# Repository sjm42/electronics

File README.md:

# Electronics
My various electronics projects

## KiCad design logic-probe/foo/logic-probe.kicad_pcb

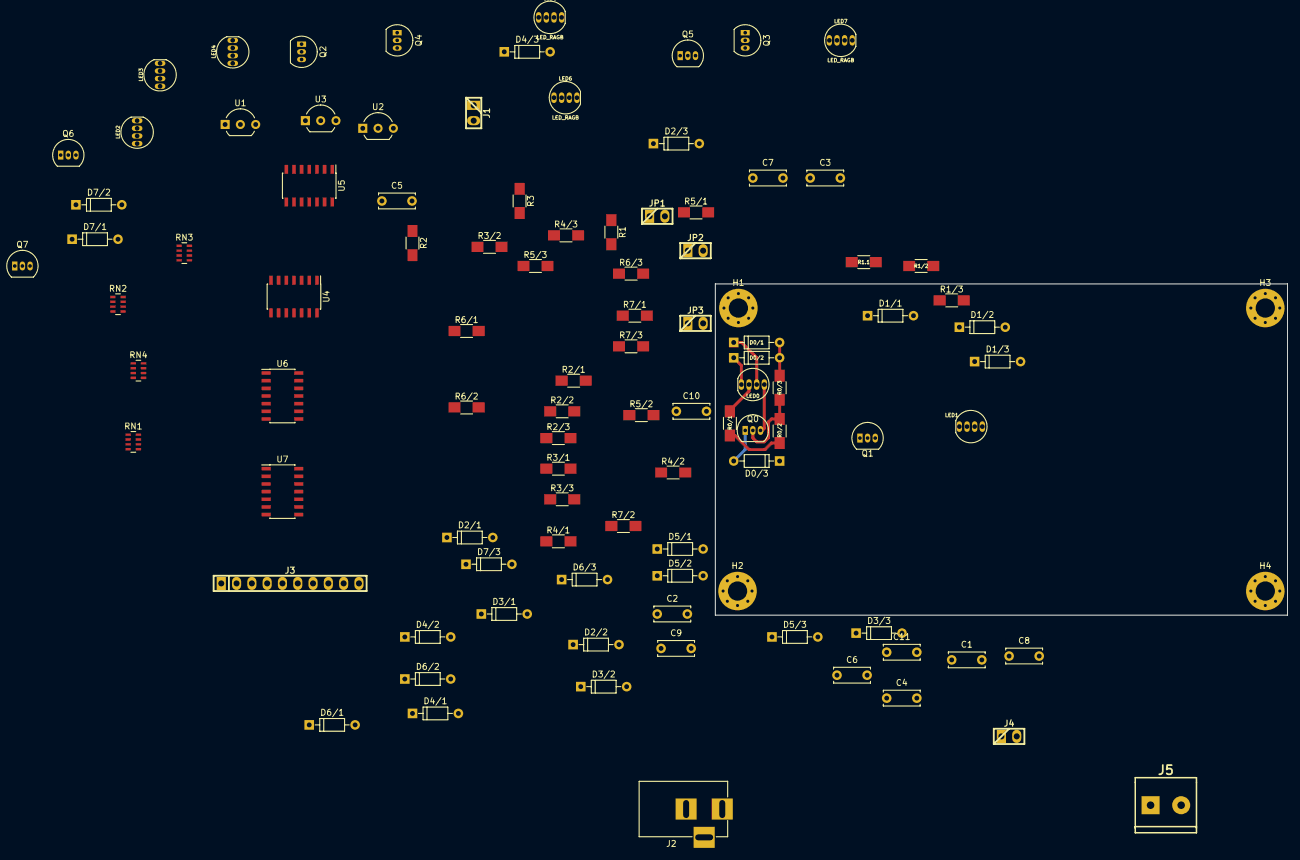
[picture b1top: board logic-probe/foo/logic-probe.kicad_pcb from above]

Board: 2 copper layers, 95.0 x 55.0 mm, 101 parts (0 on the bottom side), 72 nets.

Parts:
C1: 10u; C_Disc_D6.0mm_W2.5mm_P5.00mm
C2, C4, C6: 4.7u; C_Disc_D6.0mm_W2.5mm_P5.00mm
C3, C5, C7, C8, C9, C10, C11: 1u; C_Disc_D6.0mm_W2.5mm_P5.00mm
D0/1, D0/2, D0/3, D1/1, D1/2, D1/3, D2/1, D2/2, D2/3, D3/1, D3/2, D3/3, D4/1, D4/2, D4/3, D5/1, D5/2, D5/3, D6/1, D6/2, D6/3, D7/1, D7/2, D7/3: 1N4148; D_DO-35_SOD27_P7.62mm_Horizontal
H1, H2, H3, H4: MountingHole; MountingHole_3.2mm_M3_Pad_Via
J1, J4: Conn_01x02_Male; pin_strip_2
J2: dc_jack; BARREL_JACK
J3: Conn_01x10_Male; pin_strip_10
J5: Screw_Terminal_01x02; mors_2p
JP1, JP2, JP3: Jumper; pin_strip_2
LED0, LED1, LED2, LED3, LED4, LED5, LED6, LED7: LED_RAGB; LED-RGB-THRU
Q0, Q1, Q2, Q3, Q4, Q5, Q6, Q7: 2N2222A; TO-92_Inline_Narrow_Oval
R0/1, R1.1, R2/1, R3/1, R4/1, R5/1, R6/1, R7/1: 470; R_1206_HandSoldering
R0/2, R1/2, R2/2, R3/2, R4/2, R5/2, R6/2, R7/2: 47k; R_1206_HandSoldering
R0/3, R1/3, R2/3, R3/3, R4/3, R5/3, R6/3, R7/3: 100; R_1206_HandSoldering
R1, R3: 7.5k; R_1206_HandSoldering
R2: 10k; R_1206_HandSoldering
RN1, RN2, RN3, RN4: 220k; R_Array_Concave_4x0603
U1: L78L05_TO92; TO-92_Inline_Wide
U2: L78L10_TO92; TO-92_Inline_Wide
U3: L78L15_TO92; TO-92_Inline_Wide
U4, U5, U6, U7: LM339; SOIC-14_3.9x8.7mm_Pitch1.27mm

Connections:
/V_5V: C3.1, JP1.1, U1.1
/V_10V: C5.1, JP2.1, U2.1
/V_15V: C7.1, JP3.1, U3.1
/V_IN: C1.1, C2.1, C4.1, C6.1, J1.1, J2.3, U1.3, U2.3, U3.3
/bits/0_HI: D0/1.1, LED0.3, U4.1
/bits/0_LO: D0/2.1, LED0.1, U4.2
/bits/1_HI: D1/1.1, LED1.3, U4.13
/bits/1_LO: D1/2.1, LED1.1, U4.14
/bits/2_HI: D2/1.1, LED2.3, U5.1
/bits/2_LO: D2/2.1, LED2.1, U5.2
/bits/3_HI: D3/1.1, LED3.3, U5.13
/bits/3_LO: D3/2.1, LED3.1, U5.14
/bits/4_HI: D4/1.1, LED4.3, U6.1
/bits/4_LO: D4/2.1, LED4.1, U6.2
/bits/5_HI: D5/1.1, LED5.3, U6.13
/bits/5_LO: D5/2.1, LED5.1, U6.14
/bits/6_HI: D6/1.1, LED6.3, U7.1
/bits/6_LO: D6/2.1, LED6.1, U7.2
/bits/7_HI: D7/1.1, LED7.3, U7.13
/bits/7_LO: D7/2.1, LED7.1, U7.14
GND: C1.2, C2.2, C3.2, C4.2, C5.2, C6.2, C7.2, C8.2, C9.2, C10.2, C11.2, D0/3.1, D1/3.1, D2/3.1, D3/3.1, D4/3.1, D5/3.1, D6/3.1, D7/3.1, J1.2, J2.1, J2.2, J3.10, J4.2, J5.2, R3.2, RN2.1, RN2.2, RN2.3, RN2.4, RN4.1, RN4.2, RN4.3, RN4.4, U1.2, U2.2, U3.2, U4.12, U5.12, U6.12, U7.12
IN_0: J3.1, RN1.1, RN2.8, U4.5, U4.6
IN_1: J3.2, RN1.2, RN2.7, U4.9, U4.10
IN_2: J3.3, RN1.3, RN2.6, U5.5, U5.6
IN_3: J3.4, RN1.4, RN2.5, U5.9, U5.10
IN_4: J3.5, RN3.1, RN4.8, U6.5, U6.6
IN_5: J3.6, RN3.2, RN4.7, U6.9, U6.10
IN_6: J3.7, RN3.3, RN4.6, U7.5, U7.6
IN_7: J3.8, RN3.4, RN4.5, U7.9, U7.10
unnamed: D0/1.2, D0/2.2, R0/3.1
unnamed: D0/3.2, Q0.1
unnamed: D1/1.2, D1/2.2, R1/3.1
unnamed: D1/3.2, Q1.1
unnamed: D2/1.2, D2/2.2, R2/3.1
unnamed: D2/3.2, Q2.1
unnamed: D3/1.2, D3/2.2, R3/3.1
unnamed: D3/3.2, Q3.1
unnamed: D4/1.2, D4/2.2, R4/3.1
unnamed: D4/3.2, Q4.1
unnamed: D5/1.2, D5/2.2, R5/3.1
unnamed: D5/3.2, Q5.1
unnamed: D6/1.2, D6/2.2, R6/3.1
unnamed: D6/3.2, Q6.1
unnamed: D7/1.2, D7/2.2, R7/3.1
unnamed: D7/3.2, Q7.1
unnamed: LED0.2, R0/1.1
unnamed: LED0.4, Q0.3
unnamed: LED1.2, R1.1.1
unnamed: LED1.4, Q1.3
unnamed: LED2.2, R2/1.1
unnamed: LED2.4, Q2.3
unnamed: LED3.2, R3/1.1
unnamed: LED3.4, Q3.3
unnamed: LED4.2, R4/1.1
unnamed: LED4.4, Q4.3
unnamed: LED5.2, R5/1.1
unnamed: LED5.4, Q5.3
unnamed: LED6.2, R6/1.1
unnamed: LED6.4, Q6.3
unnamed: LED7.2, R7/1.1
unnamed: LED7.4, Q7.3
unnamed: Q0.2, R0/2.1, R0/3.2
unnamed: Q1.2, R1/2.1, R1/3.2
unnamed: Q2.2, R2/2.1, R2/3.2
unnamed: Q3.2, R3/2.1, R3/3.2
unnamed: Q4.2, R4/2.1, R4/3.2
unnamed: Q5.2, R5/2.1, R5/3.2
unnamed: Q6.2, R6/2.1, R6/3.2
unnamed: Q7.2, R7/2.1, R7/3.2
VCC: C8.1, C9.1, C10.1, C11.1, J3.9, J4.1, J5.1, JP1.2, JP2.2, JP3.2, R0/1.2, R0/2.2, R1.1, R1.1.2, R1/2.2, R2/1.2, R2/2.2, R3/1.2, R3/2.2, R4/1.2, R4/2.2, R5/1.2, R5/2.2, R6/1.2, R6/2.2, R7/1.2, R7/2.2, RN1.5, RN1.6, RN1.7, RN1.8, RN3.5, RN3.6, RN3.7, RN3.8, U4.3, U5.3, U6.3, U7.3
V_HI: R1.2, R2.1, U4.7, U4.11, U5.7, U5.11, U6.7, U6.11, U7.7, U7.11
V_LO: R2.2, R3.1, U4.4, U4.8, U5.4, U5.8, U6.4, U6.8, U7.4, U7.8

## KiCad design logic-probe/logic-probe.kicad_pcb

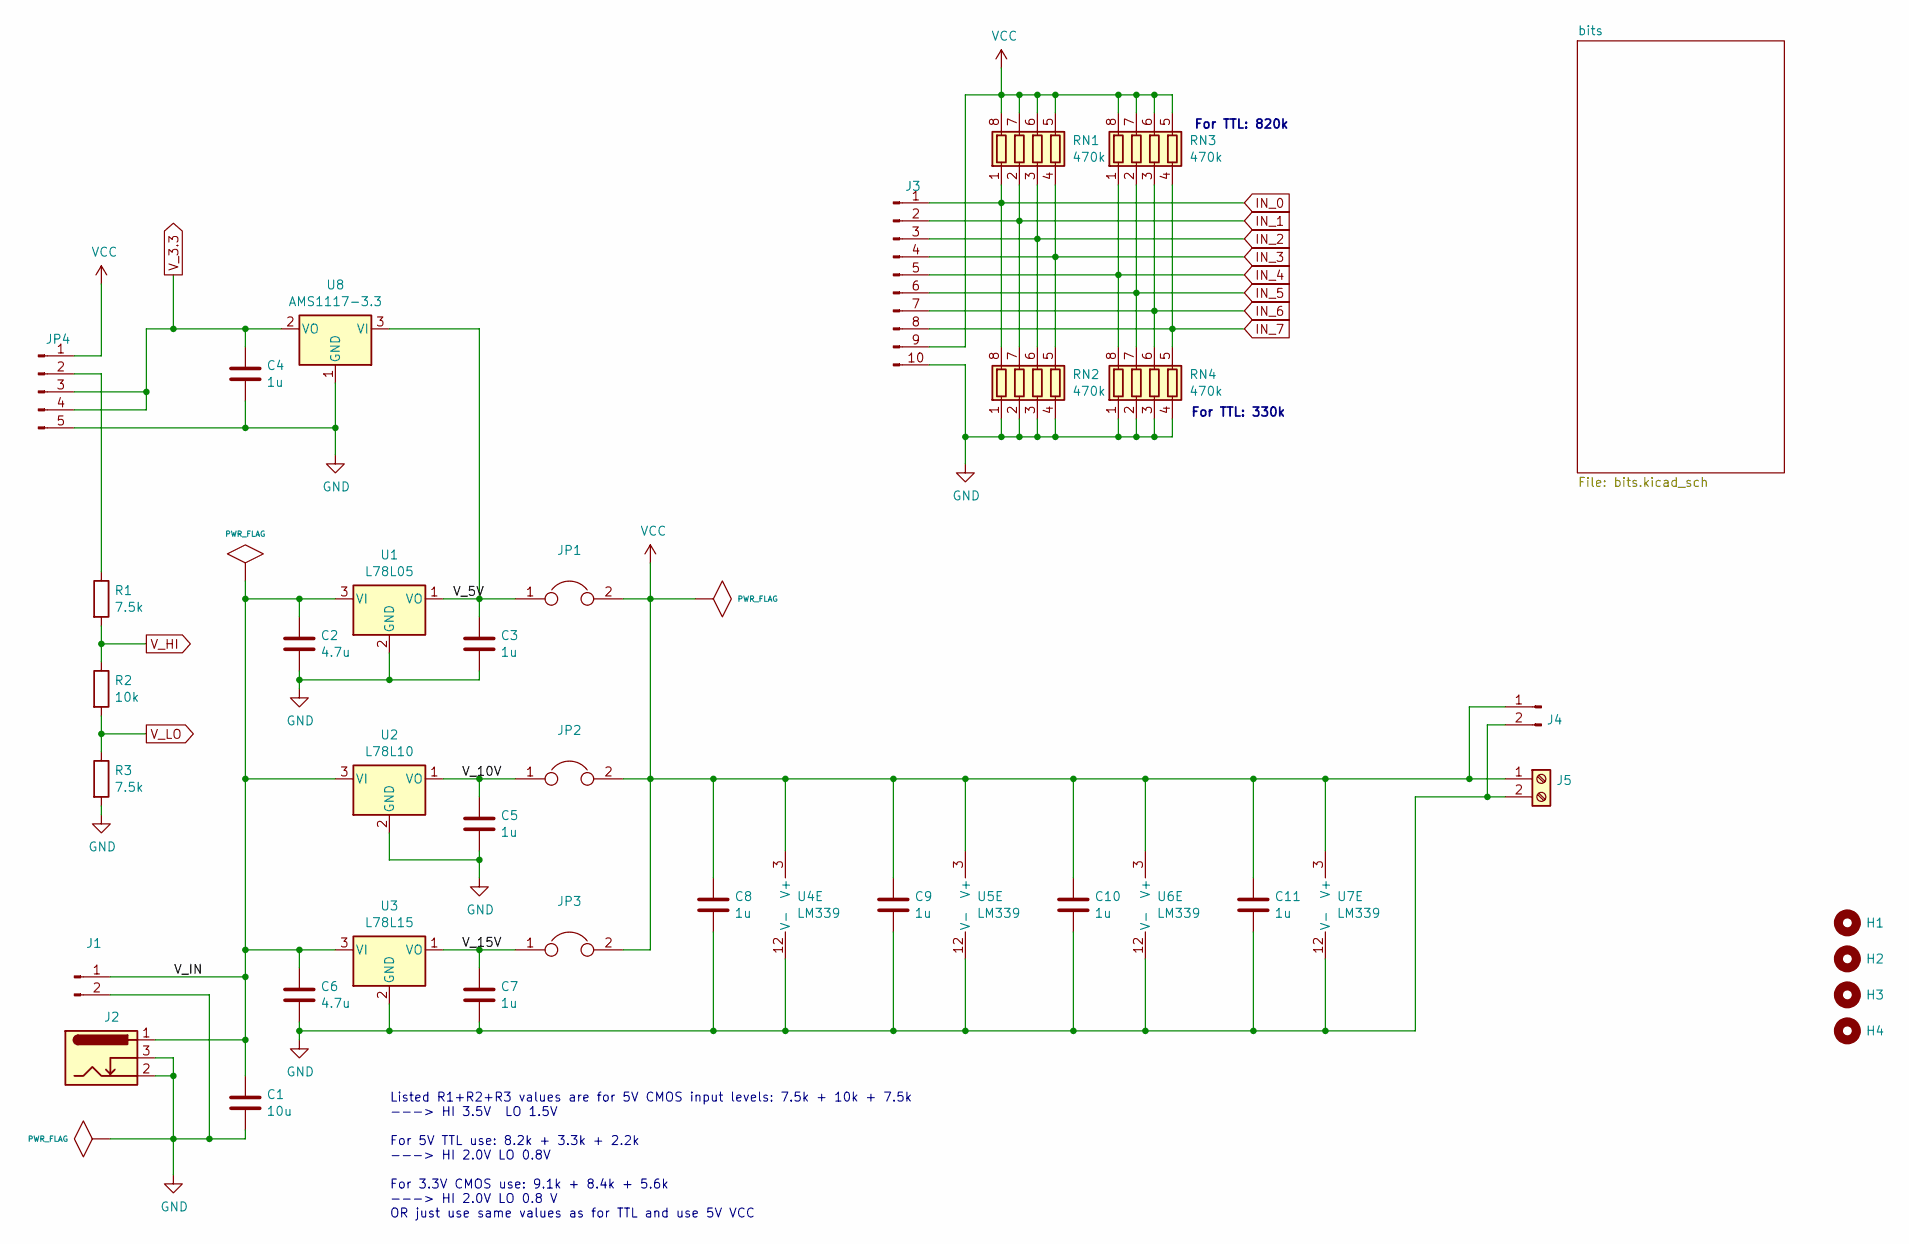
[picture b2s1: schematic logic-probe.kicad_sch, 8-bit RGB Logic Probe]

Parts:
C1: 10u; C_Disc_D6.0mm_W2.5mm_P5.00mm
C2, C6: 4.7u; C_Disc_D6.0mm_W2.5mm_P5.00mm
C3, C4, C5, C7, C8, C9, C10, C11: 1u; C_Disc_D6.0mm_W2.5mm_P5.00mm
H1, H2, H3, H4: MountingHole; MountingHole_3.2mm_M3_Pad_Via
J1, J4: Conn_01x02_Male; pin_strip_2
J2: Barrel_Jack_Switch; BarrelJack_Horizontal
J3: Conn_01x10_Male; pin_strip_10
J5: Screw_Terminal_01x02; mors_2p
JP1, JP2, JP3: Jumper; pin_strip_2
JP4: Conn_01x05_Male; pin_strip_5
R1, R3: 7.5k; R_1206_HandSoldering
R2: 10k; R_1206_HandSoldering
RN1, RN2, RN3, RN4: 470k; R_Array_Concave_4x0603
U1: L78L05; TO-92_Inline_Wide
U2: L78L10; TO-92_Inline_Wide
U3: L78L15; TO-92_Inline_Wide
U4, U5, U6, U7: LM339; SOIC-14_3.9x8.7mm_Pitch1.27mm
U8: AMS1117-3.3; sot223

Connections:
/V_5V: C3.1, JP1.1, U1.1 (VO), U8.3 (VI)
/V_10V: C5.1, JP2.1, U2.1 (VO)
/V_15V: C7.1, JP3.1, U3.1 (VO)
/V_IN: C1.1, C2.1, C6.1, J1.1, J2.1, U1.3 (VI), U2.3 (VI), U3.3 (VI)
GND: C1.2, C2.2, C3.2, C4.2, C5.2, C6.2, C7.2, C8.2, C9.2, C10.2, C11.2, J1.2, J2.2, J2.3, J3.10, J4.2, J5.2, JP4.5, R3.2, RN2.1 (R1.1), RN2.2 (R2.1), RN2.3 (R3.1), RN2.4 (R4.1), RN4.1 (R1.1), RN4.2 (R2.1), RN4.3 (R3.1), RN4.4 (R4.1), U1.2 (GND), U2.2 (GND), U3.2 (GND), U4.12 (V-), U5.12 (V-), U6.12 (V-), U7.12 (V-), U8.1 (GND); also elsewhere on the board
IN_0: J3.1, RN1.1 (R1.1), RN2.8 (R1.2); also elsewhere on the board
IN_1: J3.2, RN1.2 (R2.1), RN2.7 (R2.2); also elsewhere on the board
IN_2: J3.3, RN1.3 (R3.1), RN2.6 (R3.2); also elsewhere on the board
IN_3: J3.4, RN1.4 (R4.1), RN2.5 (R4.2); also elsewhere on the board
IN_4: J3.5, RN3.1 (R1.1), RN4.8 (R1.2); also elsewhere on the board
IN_5: J3.6, RN3.2 (R2.1), RN4.7 (R2.2); also elsewhere on the board
IN_6: J3.7, RN3.3 (R3.1), RN4.6 (R3.2); also elsewhere on the board
IN_7: J3.8, RN3.4 (R4.1), RN4.5 (R4.2); also elsewhere on the board
unnamed: JP4.2, R1.1
VCC: C8.1, C9.1, C10.1, C11.1, J3.9, J4.1, J5.1, JP1.2, JP2.2, JP3.2, JP4.1, RN1.5 (R4.2), RN1.6 (R3.2), RN1.7 (R2.2), RN1.8 (R1.2), RN3.5 (R4.2), RN3.6 (R3.2), RN3.7 (R2.2), RN3.8 (R1.2), U4.3 (V+), U5.3 (V+), U6.3 (V+), U7.3 (V+); also elsewhere on the board
V_3.3: C4.1, JP4.3, JP4.4, U8.2 (VO)
V_HI: R1.2, R2.1; also elsewhere on the board
V_LO: R2.2, R3.1; also elsewhere on the board

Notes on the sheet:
For TTL: 820k
Listed R1+R2+R3 values are for 5V CMOS input levels: 7.5k + 10k + 7.5k ---> HI 3.5V LO 1.5V For 5V TTL use: 8.2k + 3.3k + 2.2k ---> HI 2.0V LO 0.8V For 3.3V CMOS use: 9.1k + 8.4k + 5.6k ---> HI 2.0V LO 0.8 V OR just use same values as for TTL and use 5V VCC
For TTL: 330k

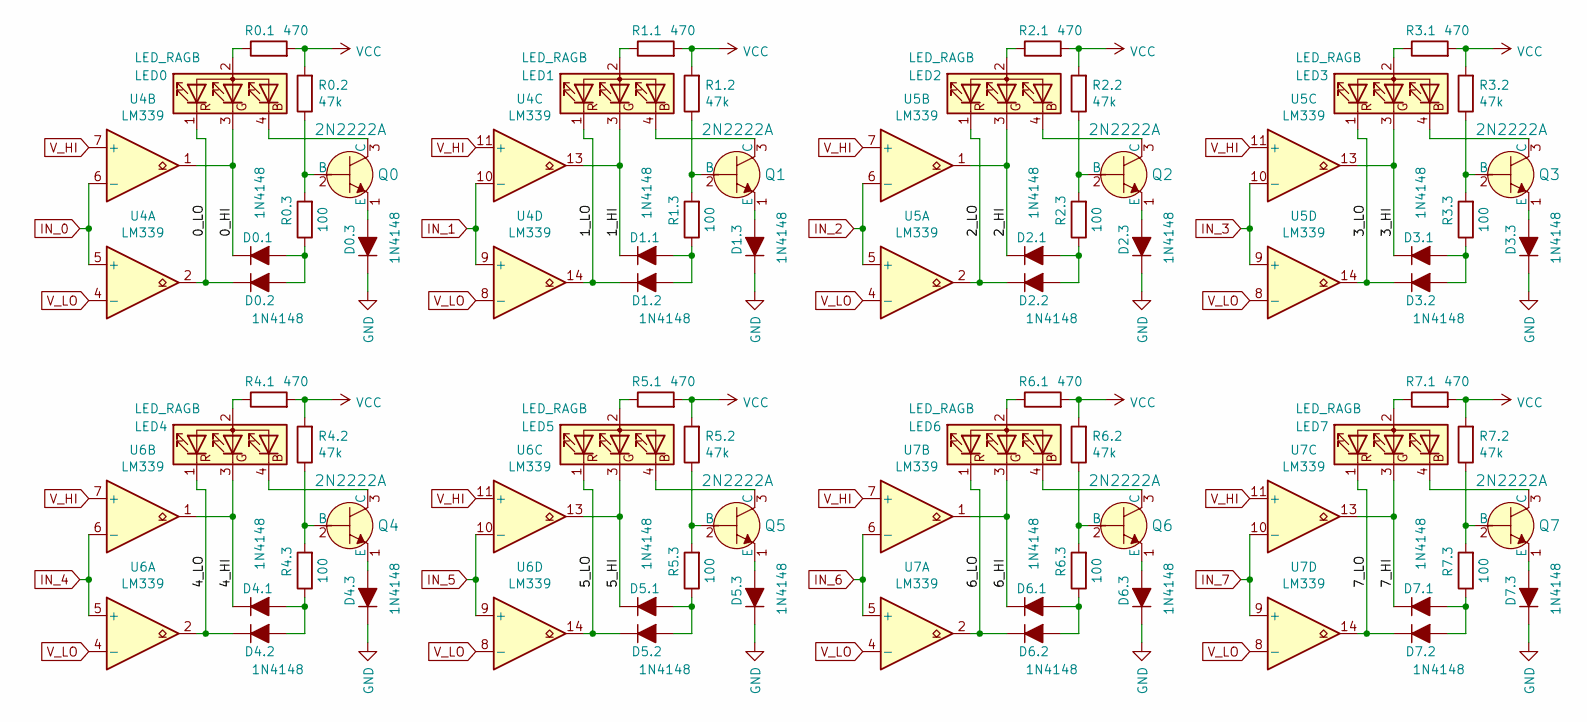
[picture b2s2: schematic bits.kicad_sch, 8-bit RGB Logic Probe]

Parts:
D0.1, D0.2, D0.3, D1.1, D1.2, D1.3, D2.1, D2.2, D2.3, D3.1, D3.2, D3.3, D4.1, D4.2, D4.3, D5.1, D5.2, D5.3, D6.1, D6.2, D6.3, D7.1, D7.2, D7.3: 1N4148; D_T-1_P5.08mm_Horizontal
LED0, LED1, LED2, LED3, LED4, LED5, LED6, LED7: LED_RAGB; LED-RGB-THRU
Q0, Q1, Q2, Q3, Q4, Q5, Q6, Q7: 2N2222A; TO-92_Inline_Narrow_Oval; MPN 2N2222A; Digi-Key_PN 2N2222ACS-ND
R0.1, R1.1, R2.1, R3.1, R4.1, R5.1, R6.1, R7.1: 470; R_1206_HandSoldering
R0.2, R1.2, R2.2, R3.2, R4.2, R5.2, R6.2, R7.2: 47k; R_1206_HandSoldering
R0.3, R1.3, R2.3, R3.3, R4.3, R5.3, R6.3, R7.3: 100; R_1206_HandSoldering
U4, U5, U6, U7: LM339; SOIC-14_3.9x8.7mm_Pitch1.27mm

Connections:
/bits/0_HI: D0.1.1 (K), LED0.3 (GK), U4.1
/bits/0_LO: D0.2.1 (K), LED0.1 (RK), U4.2
/bits/1_HI: D1.1.1 (K), LED1.3 (GK), U4.13
/bits/1_LO: D1.2.1 (K), LED1.1 (RK), U4.14
/bits/2_HI: D2.1.1 (K), LED2.3 (GK), U5.1
/bits/2_LO: D2.2.1 (K), LED2.1 (RK), U5.2
/bits/3_HI: D3.1.1 (K), LED3.3 (GK), U5.13
/bits/3_LO: D3.2.1 (K), LED3.1 (RK), U5.14
/bits/4_HI: D4.1.1 (K), LED4.3 (GK), U6.1
/bits/4_LO: D4.2.1 (K), LED4.1 (RK), U6.2
/bits/5_HI: D5.1.1 (K), LED5.3 (GK), U6.13
/bits/5_LO: D5.2.1 (K), LED5.1 (RK), U6.14
/bits/6_HI: D6.1.1 (K), LED6.3 (GK), U7.1
/bits/6_LO: D6.2.1 (K), LED6.1 (RK), U7.2
/bits/7_HI: D7.1.1 (K), LED7.3 (GK), U7.13
/bits/7_LO: D7.2.1 (K), LED7.1 (RK), U7.14
GND: D0.3.1 (K), D1.3.1 (K), D2.3.1 (K), D3.3.1 (K), D4.3.1 (K), D5.3.1 (K), D6.3.1 (K), D7.3.1 (K); also elsewhere on the board
IN_0: U4.5 (+), U4.6 (-); also elsewhere on the board
IN_1: U4.9 (+), U4.10 (-); also elsewhere on the board
IN_2: U5.5 (+), U5.6 (-); also elsewhere on the board
IN_3: U5.9 (+), U5.10 (-); also elsewhere on the board
IN_4: U6.5 (+), U6.6 (-); also elsewhere on the board
IN_5: U6.9 (+), U6.10 (-); also elsewhere on the board
IN_6: U7.5 (+), U7.6 (-); also elsewhere on the board
IN_7: U7.9 (+), U7.10 (-); also elsewhere on the board
unnamed: D0.1.2 (A), D0.2.2 (A), R0.3.1
unnamed: D0.3.2 (A), Q0.1 (E)
unnamed: D1.1.2 (A), D1.2.2 (A), R1.3.1
unnamed: D1.3.2 (A), Q1.1 (E)
unnamed: D2.1.2 (A), D2.2.2 (A), R2.3.1
unnamed: D2.3.2 (A), Q2.1 (E)
unnamed: D3.1.2 (A), D3.2.2 (A), R3.3.1
unnamed: D3.3.2 (A), Q3.1 (E)
unnamed: D4.1.2 (A), D4.2.2 (A), R4.3.1
unnamed: D4.3.2 (A), Q4.1 (E)
unnamed: D5.1.2 (A), D5.2.2 (A), R5.3.1
unnamed: D5.3.2 (A), Q5.1 (E)
unnamed: D6.1.2 (A), D6.2.2 (A), R6.3.1
unnamed: D6.3.2 (A), Q6.1 (E)
unnamed: D7.1.2 (A), D7.2.2 (A), R7.3.1
unnamed: D7.3.2 (A), Q7.1 (E)
unnamed: LED0.2 (A), R0.1.1
unnamed: LED0.4 (BK), Q0.3 (C)
unnamed: LED1.2 (A), R1.1.1
unnamed: LED1.4 (BK), Q1.3 (C)
unnamed: LED2.2 (A), R2.1.1
unnamed: LED2.4 (BK), Q2.3 (C)
unnamed: LED3.2 (A), R3.1.1
unnamed: LED3.4 (BK), Q3.3 (C)
unnamed: LED4.2 (A), R4.1.1
unnamed: LED4.4 (BK), Q4.3 (C)
unnamed: LED5.2 (A), R5.1.1
unnamed: LED5.4 (BK), Q5.3 (C)
unnamed: LED6.2 (A), R6.1.1
unnamed: LED6.4 (BK), Q6.3 (C)
unnamed: LED7.2 (A), R7.1.1
unnamed: LED7.4 (BK), Q7.3 (C)
unnamed: Q0.2 (B), R0.2.1, R0.3.2
unnamed: Q1.2 (B), R1.2.1, R1.3.2
unnamed: Q2.2 (B), R2.2.1, R2.3.2
unnamed: Q3.2 (B), R3.2.1, R3.3.2
unnamed: Q4.2 (B), R4.2.1, R4.3.2
unnamed: Q5.2 (B), R5.2.1, R5.3.2
unnamed: Q6.2 (B), R6.2.1, R6.3.2
unnamed: Q7.2 (B), R7.2.1, R7.3.2
VCC: R0.1.2, R0.2.2, R1.1.2, R1.2.2, R2.1.2, R2.2.2, R3.1.2, R3.2.2, R4.1.2, R4.2.2, R5.1.2, R5.2.2, R6.1.2, R6.2.2, R7.1.2, R7.2.2; also elsewhere on the board
V_HI: U4.7 (+), U4.11 (+), U5.7 (+), U5.11 (+), U6.7 (+), U6.11 (+), U7.7 (+), U7.11 (+); also elsewhere on the board
V_LO: U4.4 (-), U4.8 (-), U5.4 (-), U5.8 (-), U6.4 (-), U6.8 (-), U7.4 (-), U7.8 (-); also elsewhere on the board

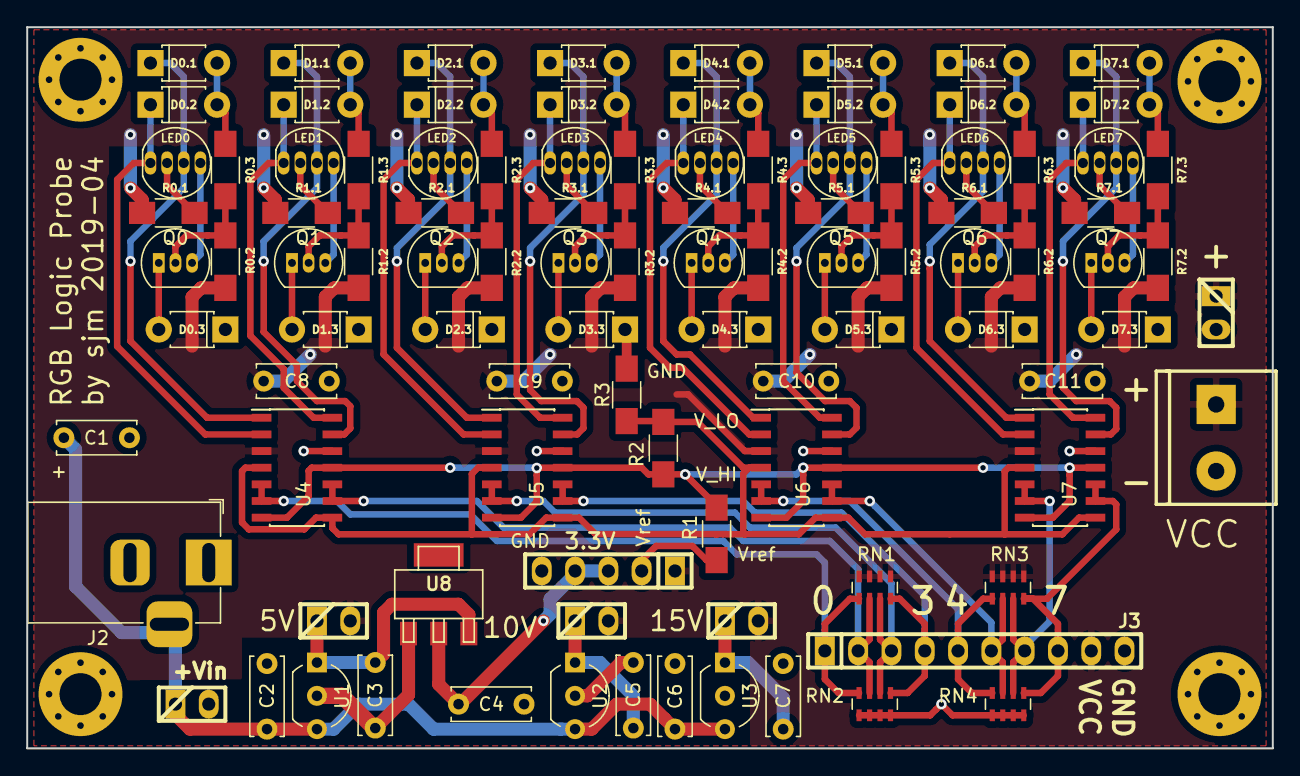
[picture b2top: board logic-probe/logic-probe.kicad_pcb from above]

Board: 2 copper layers, 95.0 x 55.0 mm, 103 parts (0 on the bottom side), 74 nets.

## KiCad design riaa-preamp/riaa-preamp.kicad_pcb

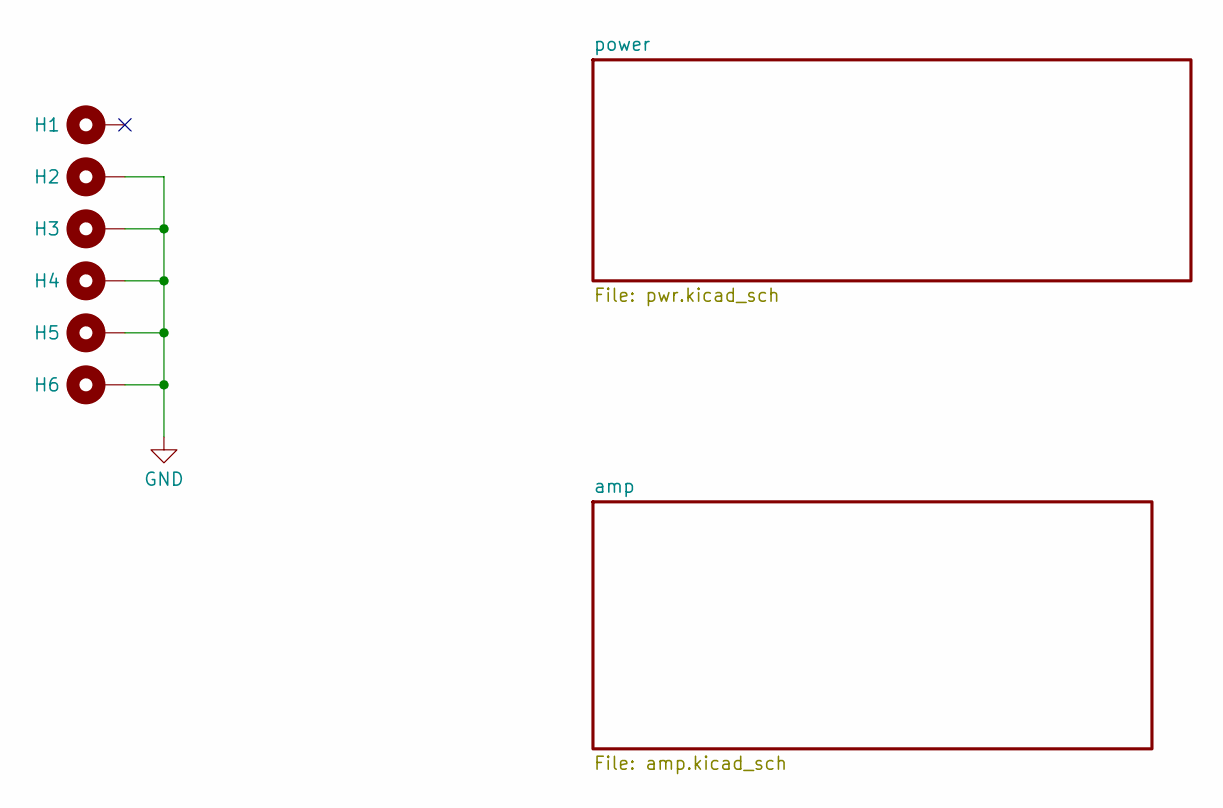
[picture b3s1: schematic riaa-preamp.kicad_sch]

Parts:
H1, H2, H3, H4: MountingHole_Pad; MountingHole_3.2mm_M3_Pad_Via
H5: MountingHole_Pad; MountingHole_6.4mm_M6_Pad_Via
H6: MountingHole_Pad; MountingHole_4.3mm_M4_Pad_Via

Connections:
GND: H2.1, H3.1, H4.1, H5.1, H6.1; also elsewhere on the board

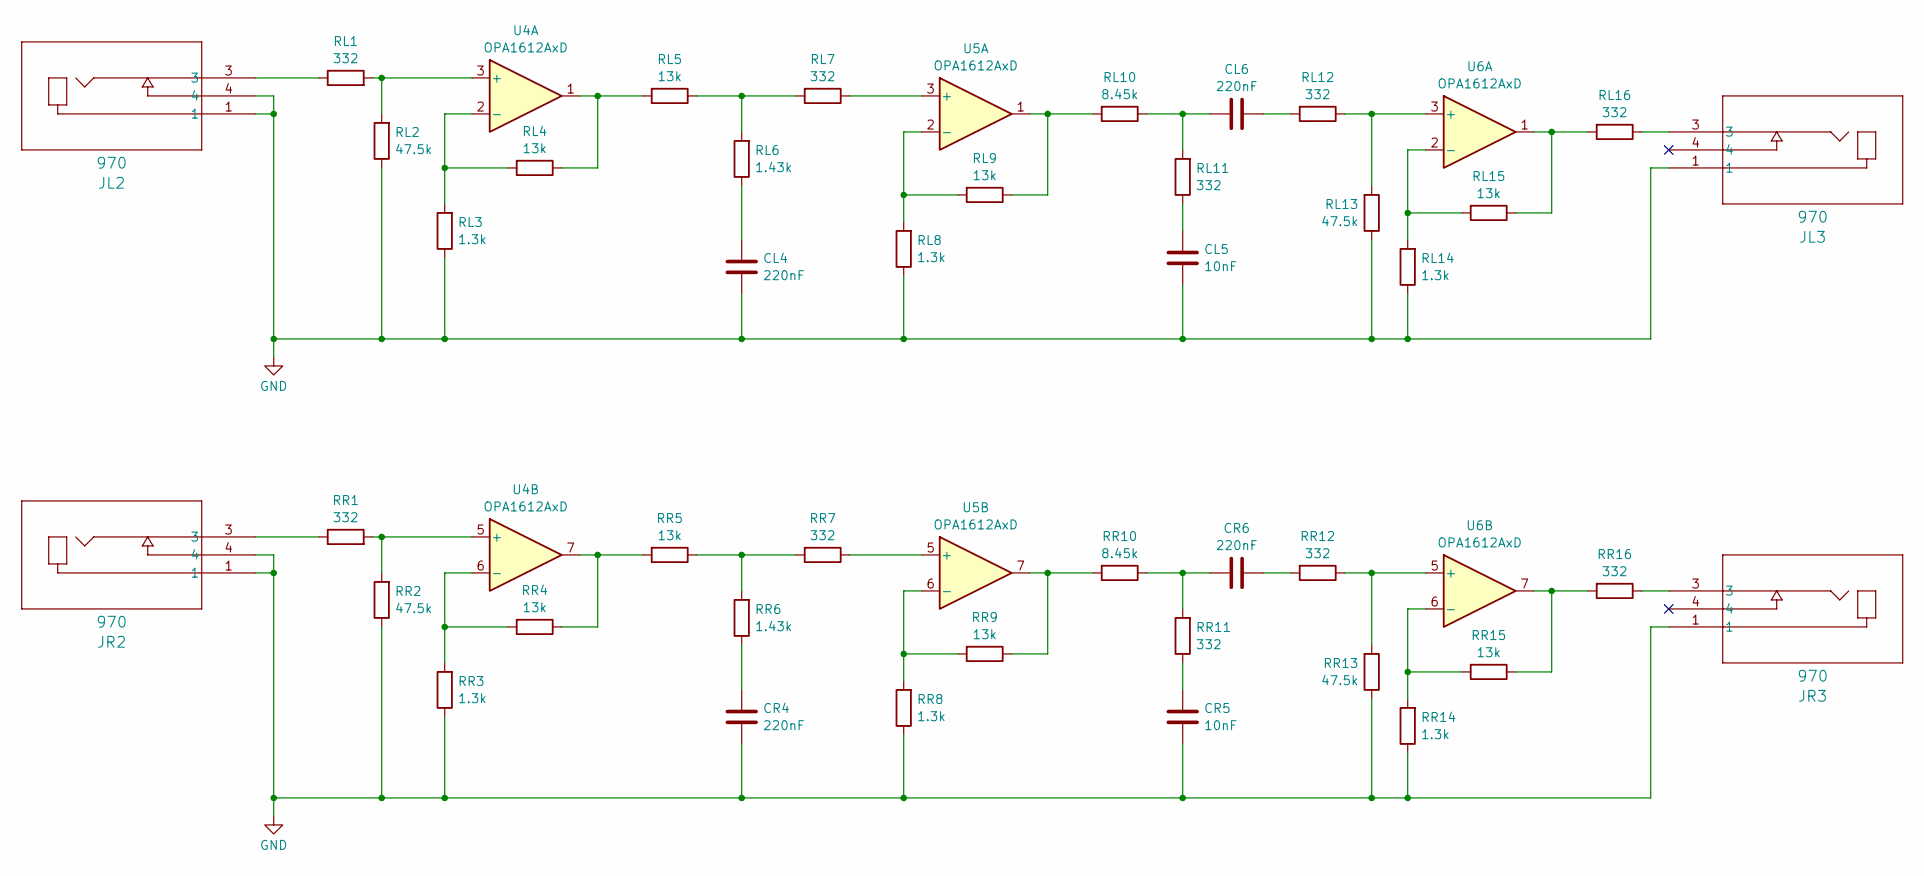
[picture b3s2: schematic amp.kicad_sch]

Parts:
CL4, CL6: 220nF; CAP_ECHUX_D4_PAN-L
CL5: 10nF; C_1206_3216Metric_Pad1.33x1.80mm_HandSolder
CR4, CR6: 220nF; CAP_ECHUX_D4_PAN-L
CR5: 10nF; C_1206_3216Metric_Pad1.33x1.80mm_HandSolder
JL2, JL3: 970; 970_KEY
JR2, JR3: 970; 970_KEY
RL1, RL7, RL11, RL12, RL16: 332; R_0805_2012Metric_Pad1.20x1.40mm_HandSolder
RL2, RL13: 47.5k; R_0805_2012Metric_Pad1.20x1.40mm_HandSolder
RL3, RL8, RL14: 1.3k; R_0805_2012Metric_Pad1.20x1.40mm_HandSolder
RL4, RL5, RL9, RL15: 13k; R_0805_2012Metric_Pad1.20x1.40mm_HandSolder
RL6: 1.43k; R_0805_2012Metric_Pad1.20x1.40mm_HandSolder
RL10: 8.45k; R_0805_2012Metric_Pad1.20x1.40mm_HandSolder
RR1, RR7, RR11, RR12, RR16: 332; R_0805_2012Metric_Pad1.20x1.40mm_HandSolder
RR2, RR13: 47.5k; R_0805_2012Metric_Pad1.20x1.40mm_HandSolder
RR3, RR8, RR14: 1.3k; R_0805_2012Metric_Pad1.20x1.40mm_HandSolder
RR4, RR5, RR9, RR15: 13k; R_0805_2012Metric_Pad1.20x1.40mm_HandSolder
RR6: 1.43k; R_0805_2012Metric_Pad1.20x1.40mm_HandSolder
RR10: 8.45k; R_0805_2012Metric_Pad1.20x1.40mm_HandSolder
U4, U5, U6: OPA1612AxD; SOIC-8_3.9x4.9mm_P1.27mm

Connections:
GND: CL4.2, CL5.2, CR4.2, CR5.2, JL2.1, JL2.4, JL3.1, JR2.1, JR2.4, JR3.1, RL2.1, RL3.1, RL8.1, RL13.1, RL14.1, RR2.1, RR3.1, RR8.1, RR13.1, RR14.1; also elsewhere on the board
unnamed: CL4.1, RL6.1
unnamed: CL5.1, RL11.1
unnamed: CL6.1, RL10.1, RL11.2
unnamed: CL6.2, RL12.2
unnamed: CR4.1, RR6.1
unnamed: CR5.1, RR11.1
unnamed: CR6.1, RR10.1, RR11.2
unnamed: CR6.2, RR12.2
unnamed: JL2.3, RL1.1
unnamed: JL3.3, RL16.1
unnamed: JR2.3, RR1.1
unnamed: JR3.3, RR16.1
unnamed: RL4.1, RL5.2, U4.1
unnamed: RL5.1, RL6.2, RL7.2
unnamed: RL9.1, RL10.2, U5.1
unnamed: RL15.1, RL16.2, U6.1
unnamed: RR4.1, RR5.2, U4.7
unnamed: RR5.1, RR6.2, RR7.2
unnamed: RR9.1, RR10.2, U5.7
unnamed: RR15.1, RR16.2, U6.7
unnamed: RL1.2, RL2.2, U4.3 (+)
unnamed: RL3.2, RL4.2, U4.2 (-)
unnamed: RR1.2, RR2.2, U4.5 (+)
unnamed: RR3.2, RR4.2, U4.6 (-)
unnamed: RL7.1, U5.3 (+)
unnamed: RL8.2, RL9.2, U5.2 (-)
unnamed: RR7.1, U5.5 (+)
unnamed: RR8.2, RR9.2, U5.6 (-)
unnamed: RL12.1, RL13.2, U6.3 (+)
unnamed: RL14.2, RL15.2, U6.2 (-)
unnamed: RR12.1, RR13.2, U6.5 (+)
unnamed: RR14.2, RR15.2, U6.6 (-)

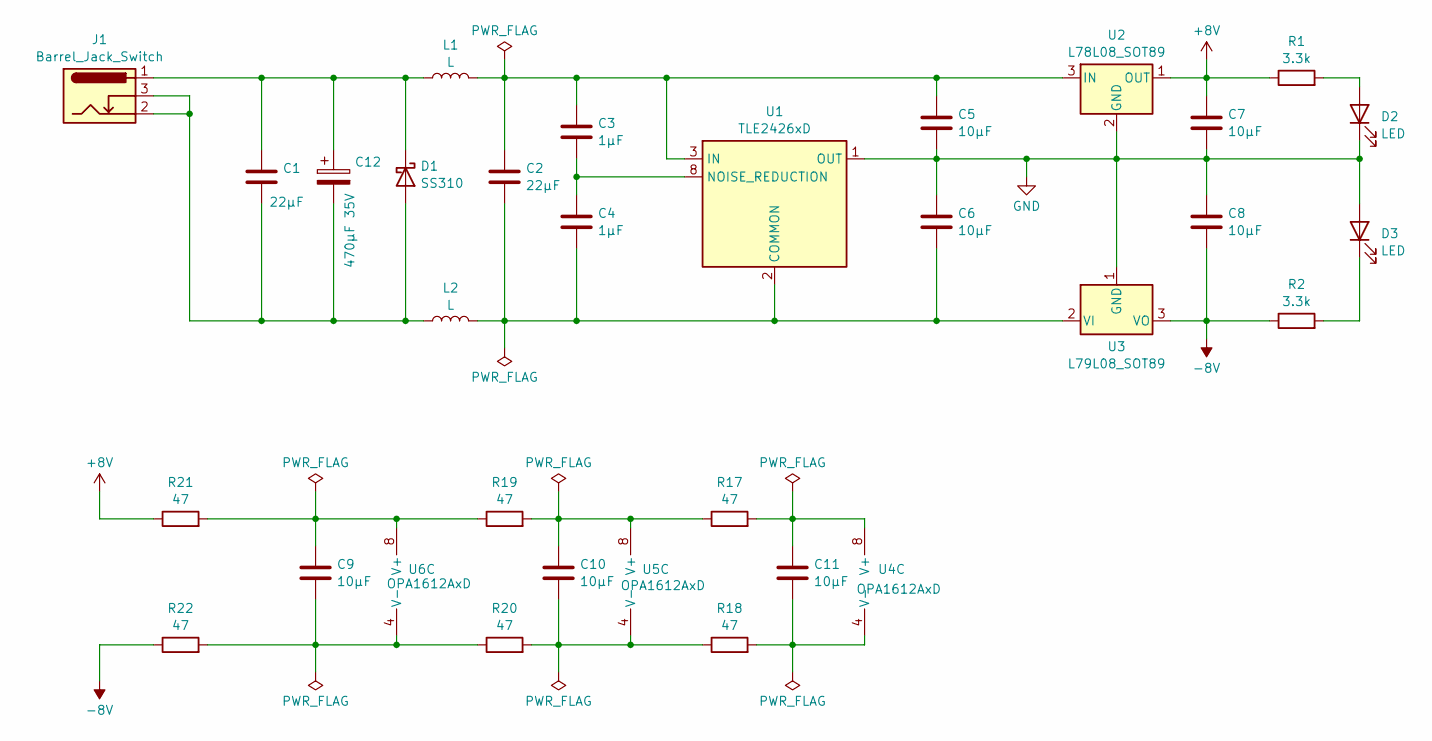
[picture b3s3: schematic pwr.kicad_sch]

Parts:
C1, C2: 22µF; C_1206_3216Metric_Pad1.33x1.80mm_HandSolder
C3, C4: 1µF; C_1206_3216Metric_Pad1.33x1.80mm_HandSolder
C5, C6, C7, C8, C9, C10, C11: 10µF; C_1206_3216Metric_Pad1.33x1.80mm_HandSolder
C12: 470µF 35V; CP_Radial_D10.0mm_P5.00mm_P7.50mm
D1: SS310; D_SMA
D2, D3: LED; LED_1206_3216Metric_Pad1.42x1.75mm_HandSolder
J1: Barrel_Jack_Switch; BarrelJack_Horizontal
L1, L2: L; L_7.3x7.3_H4.5
R1, R2: 3.3k; R_0805_2012Metric_Pad1.20x1.40mm_HandSolder
R17, R18, R19, R20, R21, R22: 47; R_0805_2012Metric_Pad1.20x1.40mm_HandSolder
U1: TLE2426xD; SOIC-8_3.9x4.9mm_P1.27mm
U2: L78L08_SOT89; SOT-89-3
U3: L79L08_SOT89; SOT-89-3
U4, U5, U6: OPA1612AxD; SOIC-8_3.9x4.9mm_P1.27mm

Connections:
+8V: C7.1, R1.1, R21.1, U2.1 (OUT)
-8V: C8.2, R2.1, R22.1, U3.3 (VO)
GND: C5.2, C6.1, C7.2, C8.1, D2.1 (K), D3.2 (A), U1.1 (OUT), U2.2 (GND), U3.1 (GND); also elsewhere on the board
unnamed: C1.2, C12.2, D1.2 (A), J1.2, J1.3, L2.1
unnamed: C1.1, C12.1, D1.1 (K), J1.1, L1.1
unnamed: D2.2 (A), R1.2
unnamed: D3.1 (K), R2.2
unnamed: C2.2, C4.2, C6.2, L2.2, U1.2 (COMMON), U3.2 (VI)
unnamed: C2.1, C3.1, C5.1, L1.2, U1.3 (IN), U2.3 (IN)
unnamed: C3.2, C4.1, U1.8 (NOISE_REDUCTION)
unnamed: C11.1, R17.2, U4.8 (V+)
unnamed: C11.2, R18.2, U4.4 (V-)
unnamed: C10.1, R17.1, R19.2, U5.8 (V+)
unnamed: C10.2, R18.1, R20.2, U5.4 (V-)
unnamed: C9.1, R19.1, R21.2, U6.8 (V+)
unnamed: C9.2, R20.1, R22.2, U6.4 (V-)

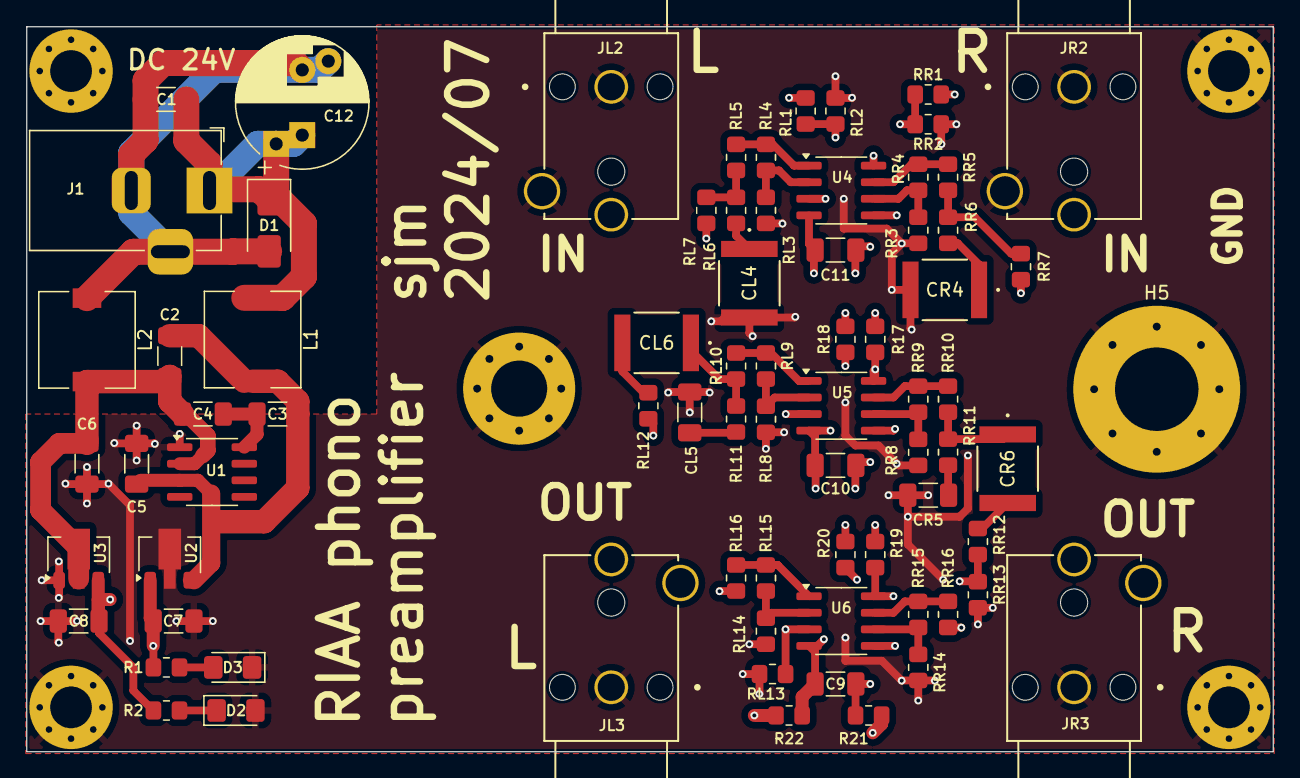
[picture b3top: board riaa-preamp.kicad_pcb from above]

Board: 4 copper layers, 95.6 x 55.6 mm, 80 parts (0 on the bottom side), 48 nets.

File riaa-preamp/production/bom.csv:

Designator,Footprint,Quantity,Value,LCSC Part #
"C1, C2",1206,2,22µF,
"C10, C11, C5, C6, C7, C8, C9",1206,7,10µF,
C12,CP_Radial_D10.0mm_P5.00mm_P7.50mm,1,470µF 35V,
"C3, C4",1206,2,1µF,
"CL4, CL6, CR4, CR6",CAP_ECHUX_D4_PAN-L,4,220nF,
"CL5, CR5",1206,2,10nF,
D1,D_SMA,1,SS310,
"D2, D3",1206,2,LED,
J1,BarrelJack_Horizontal,1,Barrel_Jack_Switch,
"JL2, JL3, JR2, JR3",970_KEY,4,970,
"L1, L2",L_7.3x7.3_H4.5,2,L,
"R1, R2",0805,2,3.3k,
"R17, R18, R19, R20, R21, R22",0805,6,47,
"RL1, RL11, RL12, RL16, RL7, RR1, RR11, RR12, RR16, RR7",0805,10,332,
"RL10, RR10",0805,2,8.45k,
"RL13, RL2, RR13, RR2",0805,4,47.5k,
"RL14, RL3, RL8, RR14, RR3, RR8",0805,6,1.3k,
"RL15, RL4, RL5, RL9, RR15, RR4, RR5, RR9",0805,8,13k,
"RL6, RR6",0805,2,1.43k,
U1,SOIC-8_3.9x4.9mm_P1.27mm,1,TLE2426xD,
U2,SOT-89-3,1,L78L08_SOT89,
U3,SOT-89-3,1,L79L08_SOT89,
"U4, U5, U6",SOIC-8_3.9x4.9mm_P1.27mm,3,OPA1612AxD,

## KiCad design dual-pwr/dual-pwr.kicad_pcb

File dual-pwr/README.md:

# Dual-pwr

I got this inspiration from the book **1001 Circuits** by _Elektor_.
The circuit is titled **Turning your Bench Supply into a Dual Supply**.

I added a fuse, a few diodes for protection and a trimmer for fine adjustment of the "ground" level.

Practically any dual opamp should work well, for example LM358, TL072 or any else with a compatible pinout. Just select one with a large enough supply voltage range. Since this circuit is basically a voltage follower (gain=1) for DC, equipped with bypass capacitors for transients, we just don't need high bandwidth, low offsets, high slew rate or any fancy features from the opamp.

-sjm

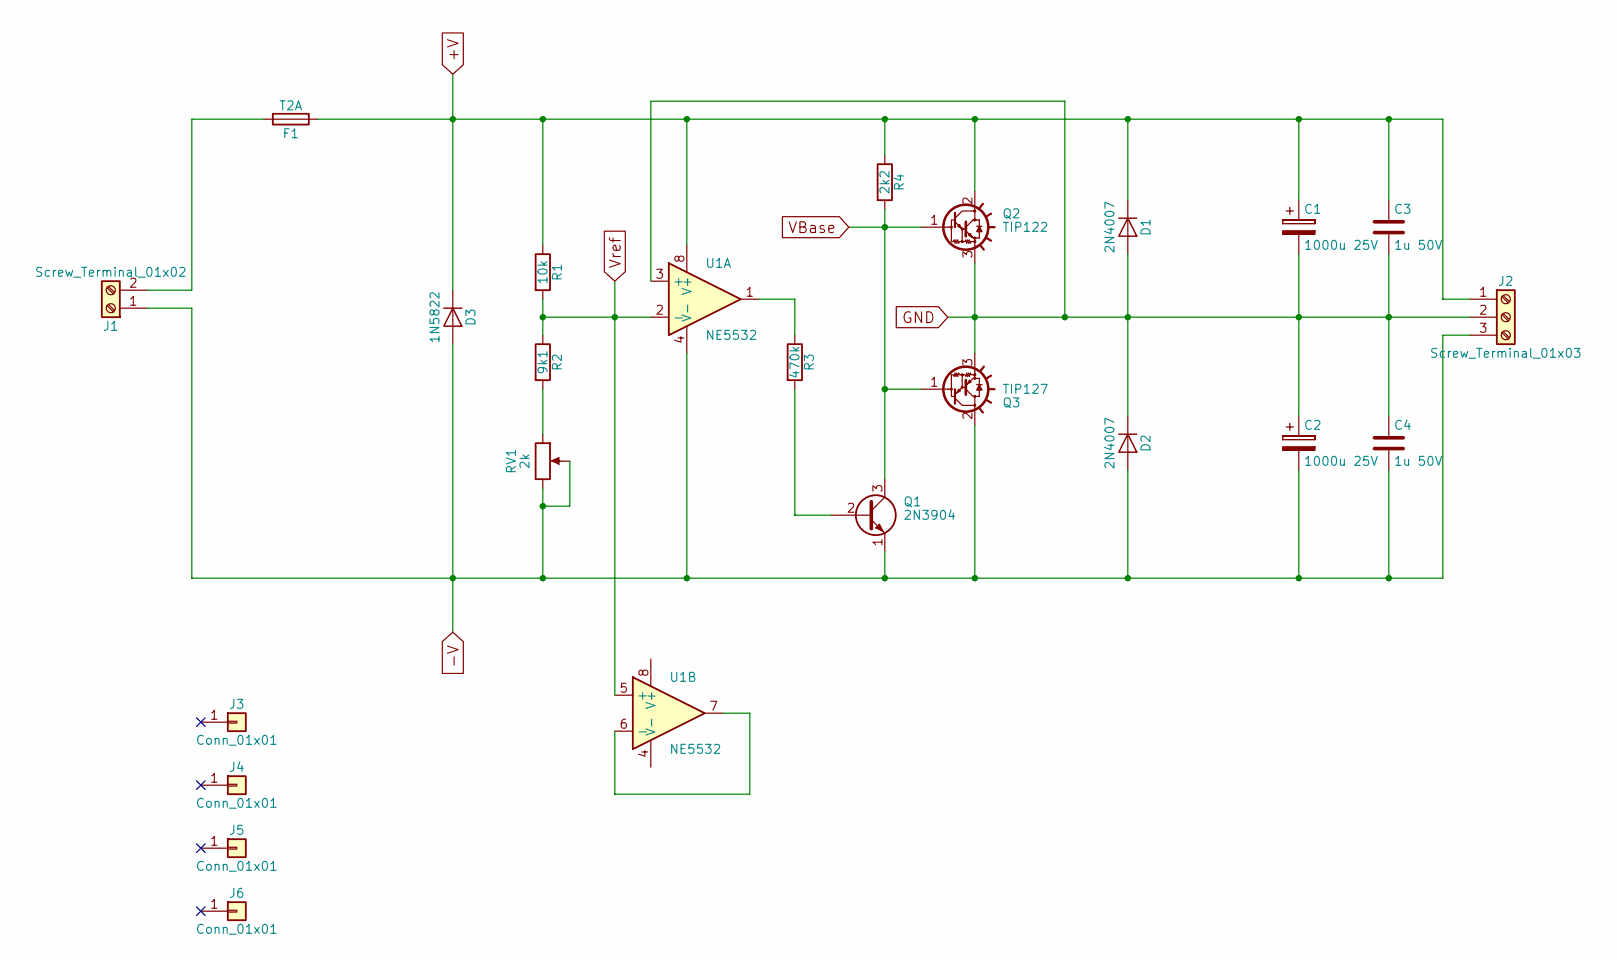
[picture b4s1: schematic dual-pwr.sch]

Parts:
C1, C2: 1000u 25V; CP_Radial_D10.0mm_P5.00mm
C3, C4: 1u 50V; C_Disc_D5.0mm_W2.5mm_P5.00mm
D1, D2: 2N4007; D_DO-41_SOD81_P10.16mm_Horizontal
D3: 1N5822; D_DO-27_P15.24mm_Horizontal
F1: T2A; Fuseholder5x20_horiz_open_universal_Type-III
J1: Screw_Terminal_01x02; pt_1,5-2-3,5-h
J2: Screw_Terminal_01x03; pt_1,5-3-3,5-h
J3, J4, J5, J6: Conn_01x01; MountingHole_3.2mm_M3_Pad_Via
Q1: 2N3904; TO-92_Molded_Narrow
Q2: TIP122; TO-220-3_Vertical
Q3: TIP127; TO-220-3_Vertical
R1: 10k; R_Axial_DIN0207_L6.3mm_D2.5mm_P7.62mm_Horizontal
R2: 9k1; R_Axial_DIN0207_L6.3mm_D2.5mm_P7.62mm_Horizontal
R3: 470k; R_Axial_DIN0207_L6.3mm_D2.5mm_P7.62mm_Horizontal
R4: 2k2; R_Axial_DIN0207_L6.3mm_D2.5mm_P7.62mm_Horizontal
RV1: 2k; Potentiometer_Trimmer_Vishay_T73XW_Vertical
U1: NE5532; DIP-8_W7.62mm_Socket

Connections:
+V: C1.1, C3.1, D1.1 (K), D3.1 (K), F1.1, J2.1, Q2.2 (C), R1.1, R4.1, U1.8 (V+)
-V: C2.2, C4.2, D2.2 (A), D3.2 (A), J1.1, J2.3, Q1.1 (E), Q3.2 (C), RV1.2, RV1.3, U1.4 (V-)
GND: C1.2, C2.1, C3.2, C4.1, D1.2 (A), D2.1 (K), J2.2, Q2.3 (E), Q3.3 (E), U1.3 (+)
unnamed: F1.2, J1.2
unnamed: Q1.2 (B), R3.2
unnamed: R2.2, RV1.1
unnamed: R3.1, U1.1
unnamed: U1.6 (-), U1.7
VBase: Q1.3 (C), Q2.1 (B), Q3.1 (B), R4.2
Vref: R1.2, R2.1, U1.2 (-), U1.5 (+)
